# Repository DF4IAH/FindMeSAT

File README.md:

# FindMeSAT
GPS assisted tracking device with GSM (SMS & GPRS) and Bluetooth connectivity.

## List of devices
* __CPU: Atmel ATxmega256A3BU__ (256kB Flash / 16kB RAM / 4kB EEPROM)
* __GSM / GPS / BT: SIM808__ (SMS / GPRS / ...)
* __VHF/UHF: AX5243__ (VHF TX/RX)
* __Accel/Gyro/Mag: MPU-9250__ (3Axis-Acceleration, 3Axis-Gyro, 3Axis-Magneto)
* __Baro/Temp: MS560702BA03-50__ (0.2 meter height resolution, better than 0.01°C resolution)
* __Hygro: SHT31-DIS__ (hygrometer within the air stream of the board)
* __VCTCXO: CFPT-141_20MHz__ (being synchronized to the GPS 1PPS signal by pulling the VC)
* __GSM antenna: within the PCB__ (works for each band)
* __BT antenna: within the PCB__ (not used yet)
* __GPS antenna: external active antenna__ via MCX connector
* __VHF/UHF antenna: external passive antenna__ via SMA connector
* __LiPo: 1-cell 3.7V__ (high power request by the SIM808 device to be satisfied)

### Current PCB overview:

### Working Tracker application with GPRS, APRS and POCSAG transmission:

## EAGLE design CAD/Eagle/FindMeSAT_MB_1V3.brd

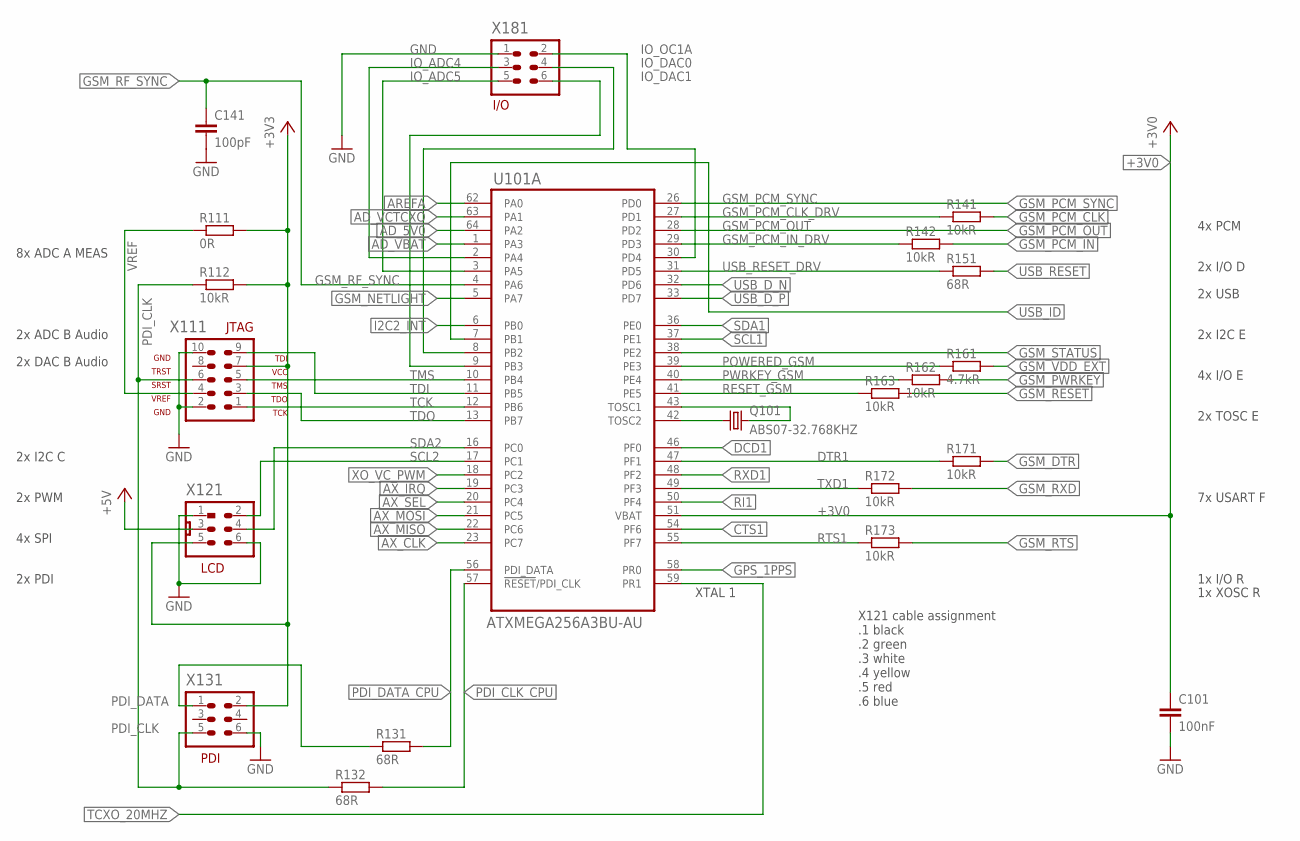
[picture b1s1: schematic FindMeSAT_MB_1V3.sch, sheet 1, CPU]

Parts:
C101: 100nF; C0603
C141: 100pF; C0603
Q101: ABS07-32.768KHZ; ABS07
R111: 0R; R0805
R112, R141, R142, R162, R163, R171, R172, R173: 10kR; R0603
R131, R132, R151: 68R; R0603
R161: 4.7kR; R0603
U101: ATXMEGA256A3BU-AU; QFP80P1600X1600X120-64N
X111: AVR-JTAG-10
X121: MOLEX_90130_2X03
X131, X181: HEADER-2X3; 2X03

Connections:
+3V0: C101.1, U101.51 (VBAT); also elsewhere on the board
+3V3: R111.2, R112.2, X111.7, X121.5, X131.2; also elsewhere on the board
+5V: X121.3; also elsewhere on the board
AD_5V0: U101.64 (PA2); also elsewhere on the board
AD_VBAT: U101.1 (PA3); also elsewhere on the board
AD_VCTCXO: U101.63 (PA1); also elsewhere on the board
AREFA: U101.62 (PA0); also elsewhere on the board
AX_CLK: U101.23 (PC7); also elsewhere on the board
AX_IRQ: U101.19 (PC3); also elsewhere on the board
AX_MISO: U101.22 (PC6); also elsewhere on the board
AX_MOSI: U101.21 (PC5); also elsewhere on the board
AX_SEL: U101.20 (PC4); also elsewhere on the board
CTS1: U101.54 (PF6); also elsewhere on the board
DCD1: U101.46 (PF0); also elsewhere on the board
DTR1: R171.1, U101.47 (PF1)
GND: C101.2, C141.2, X111.2, X111.10, X121.1, X121.6, X131.6, X181.1; also elsewhere on the board
GPS_1PPS: U101.58 (PR0); also elsewhere on the board
GSM_DTR: R171.2; also elsewhere on the board
GSM_NETLIGHT: U101.5 (PA7); also elsewhere on the board
GSM_PCM_CLK: R141.2; also elsewhere on the board
GSM_PCM_CLK_DRV: R141.1, U101.27 (PD1)
GSM_PCM_IN: R142.2; also elsewhere on the board
GSM_PCM_IN_DRV: R142.1, U101.29 (PD3)
GSM_PCM_OUT: U101.28 (PD2); also elsewhere on the board
GSM_PCM_SYNC: U101.26 (PD0); also elsewhere on the board
GSM_PWRKEY: R162.2; also elsewhere on the board
GSM_RESET: R163.2; also elsewhere on the board
GSM_RF_SYNC: C141.1, U101.4 (PA6); also elsewhere on the board
GSM_RTS: R173.2; also elsewhere on the board
GSM_RXD: R172.2; also elsewhere on the board
GSM_STATUS: U101.38 (PE2); also elsewhere on the board
GSM_VDD_EXT: R161.2; also elsewhere on the board
I2C2_INT: U101.6 (PB0); also elsewhere on the board
IO_ADC4: U101.2 (PA4), X181.3
IO_ADC5: U101.3 (PA5), X181.5
IO_DAC0: U101.8 (PB2), X181.4
IO_DAC1: U101.9 (PB3), X181.6
IO_OC1A: U101.30 (PD4), X181.2
PDI_CLK: R112.1, R132.1, X111.6, X131.5
PDI_CLK_CPU: R132.2, U101.57 (!RESET!/PDI_CLK)
PDI_DATA: R131.1, X131.1
PDI_DATA_CPU: R131.2, U101.56 (PDI_DATA)
POWERED_GSM: R161.1, U101.39 (PE3)
PWRKEY_GSM: R162.1, U101.40 (PE4)
RESET_GSM: R163.1, U101.41 (PE5)
RI1: U101.50 (PF4); also elsewhere on the board
RTS1: R173.1, U101.55 (PF7)
RXD1: U101.48 (PF2); also elsewhere on the board
SCL1: U101.37 (PE1); also elsewhere on the board
SCL2: U101.17 (PC1), X121.2
SDA1: U101.36 (PE0); also elsewhere on the board
SDA2: U101.16 (PC0), X121.4
TCK: U101.12 (PB6), X111.1
TCXO_20MHZ: U101.59 (PR1); also elsewhere on the board
TDI: U101.11 (PB5), X111.9
TDO: U101.13 (PB7), X111.3
TMS: U101.10 (PB4), X111.5
TOSC1: Q101.2, U101.43 (TOSC1)
TOSC2: Q101.1, U101.42 (TOSC2)
TXD1: R172.1, U101.49 (PF3)
USB_D_N: U101.32 (PD6); also elsewhere on the board
USB_D_P: U101.33 (PD7); also elsewhere on the board
USB_ID: U101.7 (PB1); also elsewhere on the board
USB_RESET: R151.2; also elsewhere on the board
USB_RESET_DRV: R151.1, U101.31 (PD5)
VREF: R111.1, X111.4
XO_VC_PWM: U101.18 (PC2); also elsewhere on the board

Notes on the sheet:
XTAL 1
PDI
2x ADC B Audio
8x ADC A MEAS
2x PWM
4x SPI
2x I2C C
2x I2C E
2x USB
4x PCM
7x USART F
4x I/O E
2x TOSC E
1x I/O R
1x XOSC R
2x I/O D
2x PDI
2x DAC B Audio
LCD
I/O
X121 cable assignment .1 black .2 green .3 white .4 yellow .5 red .6 blue

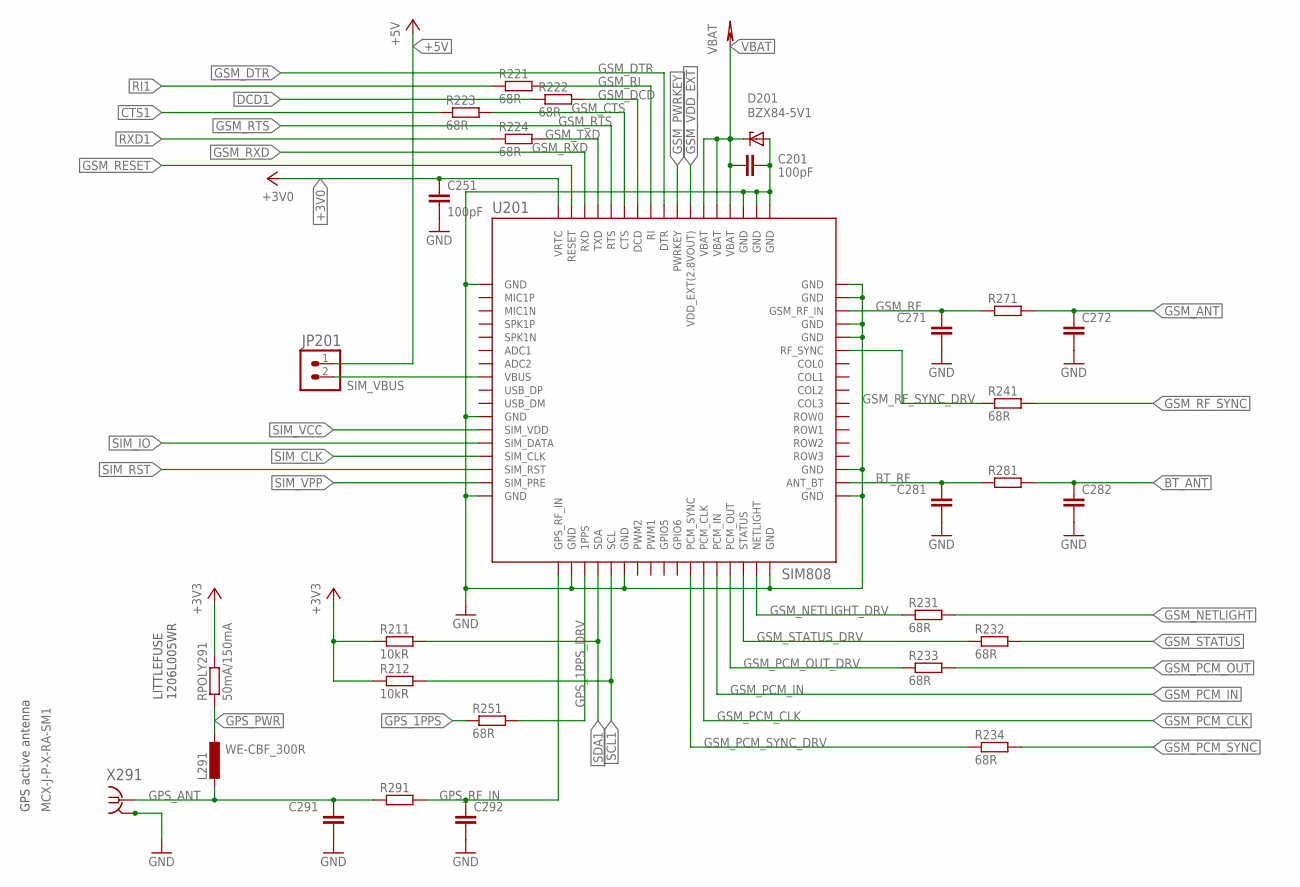
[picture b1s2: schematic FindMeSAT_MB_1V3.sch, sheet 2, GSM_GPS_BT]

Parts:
C201, C251: 100pF; C0603
C271, C272, C281, C282, C291, C292: C-EUC0603; C0603
D201: BZX84-5V1; TO236
JP201: POW; 1X02
L291: WE-CBF_300R; L3216C
R211, R212: 10kR; R0603
R221, R222, R223, R224, R231, R232, R233, R234, R241, R251: 68R; R0603
R271, R281: R-EU_R0805; R0805
R291: R-EU_R0603; R0603
RPOLY291: 50mA/150mA; R1210
U201: SIM808
X291: MCX-J-P-X-RA-SM1

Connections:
+3V0: C251.1, U201.17 (VRTC); also elsewhere on the board
+3V3: R211.1, R212.1, RPOLY291.2; also elsewhere on the board
+5V: JP201.1; also elsewhere on the board
BT_ANT: C282.1, R281.2
BT_RF: C281.1, R281.1, U201.53 (ANT_BT)
CTS1: R223.1; also elsewhere on the board
DCD1: R222.1; also elsewhere on the board
GND: C201.2, C251.2, C271.2, C272.2, C281.2, C282.2, C291.2, C292.2, D201.A, U201.1 (GND), U201.2 (GND), U201.3 (GND), U201.18 (GND), U201.28 (GND), U201.34 (GND), U201.36 (GND), U201.40 (GND), U201.51 (GND), U201.52 (GND), U201.54 (GND), U201.64 (GND), U201.65 (GND), U201.67 (GND), U201.68 (GND), X291.2, X291.3, X291.4, X291.5; also elsewhere on the board
GPS_1PPS: R251.1; also elsewhere on the board
GPS_1PPS_DRV: R251.2, U201.37 (1PPS)
GPS_ANT: C291.1, L291.2, R291.1, X291.1
GPS_PWR: L291.1, RPOLY291.1
GPS_RF_IN: C292.1, R291.2, U201.35 (GPS_RF_IN)
GSM_ANT: C272.1, R271.2
GSM_CTS: R223.2, U201.12 (CTS)
GSM_DCD: R222.2, U201.11 (DCD)
GSM_DTR: U201.9 (DTR); also elsewhere on the board
GSM_NETLIGHT: R231.2; also elsewhere on the board
GSM_NETLIGHT_DRV: R231.1, U201.50 (NETLIGHT)
GSM_PCM_CLK: U201.46 (PCM_CLK); also elsewhere on the board
GSM_PCM_IN: U201.47 (PCM_IN); also elsewhere on the board
GSM_PCM_OUT: R233.2; also elsewhere on the board
GSM_PCM_OUT_DRV: R233.1, U201.48 (PCM_OUT)
GSM_PCM_SYNC: R234.2; also elsewhere on the board
GSM_PCM_SYNC_DRV: R234.1, U201.45 (PCM_SYNC)
GSM_PWRKEY: U201.8 (PWRKEY); also elsewhere on the board
GSM_RESET: U201.16 (RESET); also elsewhere on the board
GSM_RF: C271.1, R271.1, U201.66 (GSM_RF_IN)
GSM_RF_SYNC: R241.2; also elsewhere on the board
GSM_RF_SYNC_DRV: R241.1, U201.63 (RF_SYNC)
GSM_RI: R221.2, U201.10 (RI)
GSM_RTS: U201.13 (RTS); also elsewhere on the board
GSM_RXD: U201.15 (RXD); also elsewhere on the board
GSM_STATUS: R232.2; also elsewhere on the board
GSM_STATUS_DRV: R232.1, U201.49 (STATUS)
GSM_TXD: R224.2, U201.14 (TXD)
GSM_VDD_EXT: U201.7 (VDD_EXT(2.8VOUT)); also elsewhere on the board
RI1: R221.1; also elsewhere on the board
RXD1: R224.1; also elsewhere on the board
SCL1: R212.2, U201.39 (SCL); also elsewhere on the board
SDA1: R211.2, U201.38 (SDA); also elsewhere on the board
SIM_CLK: U201.31 (SIM_CLK); also elsewhere on the board
SIM_IO: U201.30 (SIM_DATA); also elsewhere on the board
SIM_RST: U201.32 (SIM_RST); also elsewhere on the board
SIM_VBUS: JP201.2, U201.25 (VBUS)
SIM_VCC: U201.29 (SIM_VDD); also elsewhere on the board
SIM_VPP: U201.33 (SIM_PRE); also elsewhere on the board
VBAT: C201.1, D201.C, U201.4 (VBAT), U201.5 (VBAT), U201.6 (VBAT); also elsewhere on the board

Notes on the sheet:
LITTLEFUSE 1206L005WR
GPS active antenna

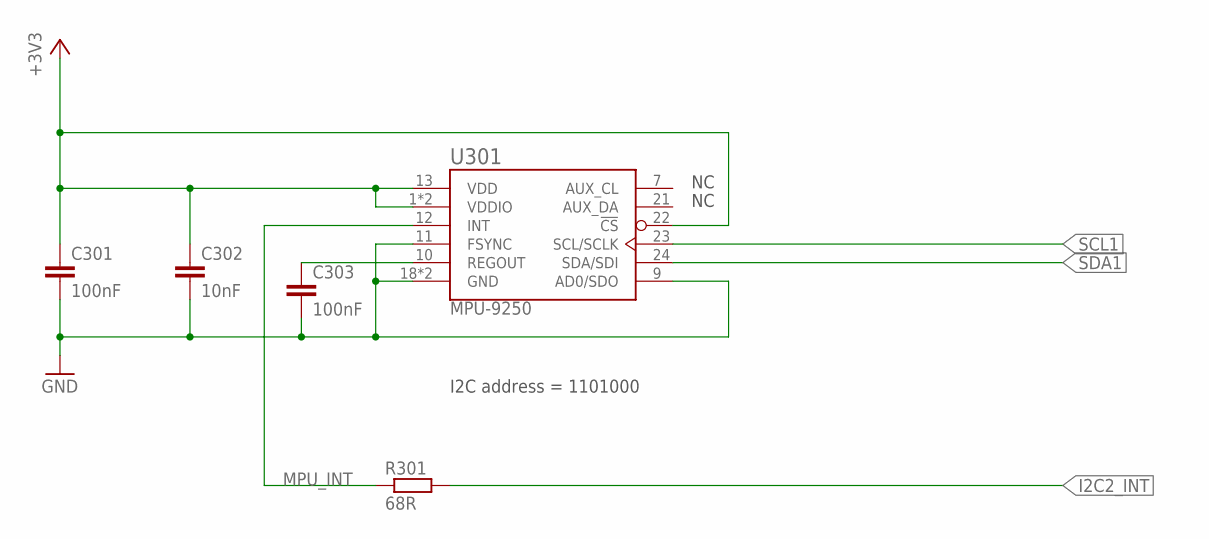
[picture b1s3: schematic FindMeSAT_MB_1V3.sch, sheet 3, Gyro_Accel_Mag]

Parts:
C301, C303: 100nF; C0603
C302: 10nF; C0603
R301: 68R; R0603
U301: MPU-9250; QFN24-3X3

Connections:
+3V3: C301.1, C302.1, U301.1 (VDDIO), U301.8 (VDDIO), U301.13 (VDD), U301.22 (!CS); also elsewhere on the board
GAM_RO: C303.1, U301.10 (REGOUT)
GND: C301.2, C302.2, C303.2, U301.9 (AD0/SDO), U301.11 (FSYNC), U301.18 (GND), U301.20 (GND); also elsewhere on the board
I2C2_INT: R301.2; also elsewhere on the board
MPU_INT: R301.1, U301.12 (INT)
SCL1: U301.23 (SCL/SCLK); also elsewhere on the board
SDA1: U301.24 (SDA/SDI); also elsewhere on the board

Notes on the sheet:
I2C address = 1101000

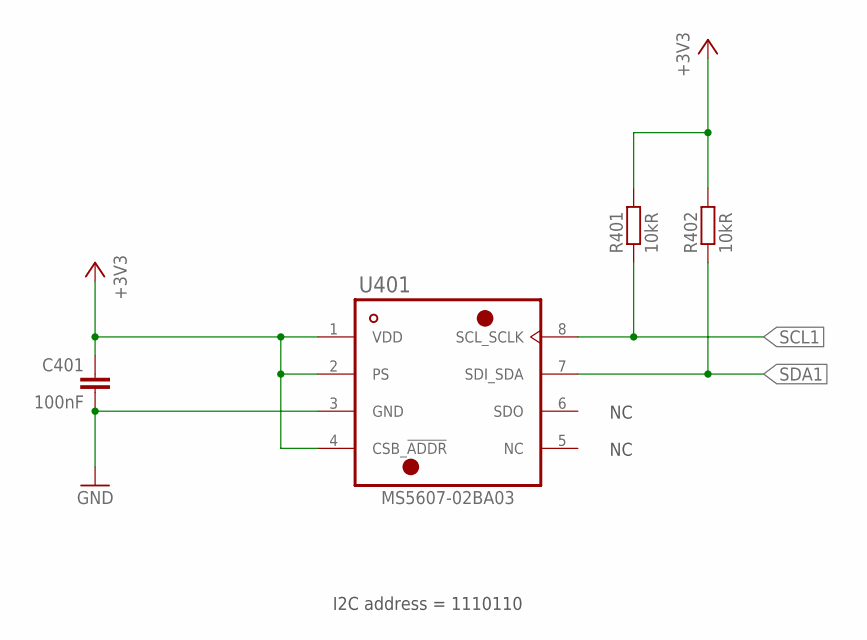
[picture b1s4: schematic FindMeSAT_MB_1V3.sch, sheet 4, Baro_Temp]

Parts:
C401: 100nF; C0603
R401, R402: 10kR; R0603
U401: MS5607-02BA03; MS5607-02BA

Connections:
+3V3: C401.1, R401.2, R402.2, U401.1 (VDD), U401.2 (PS), U401.4 (CSB_!ADDR); also elsewhere on the board
GND: C401.2, U401.3 (GND); also elsewhere on the board
SCL1: R401.1, U401.8 (SCL_SCLK); also elsewhere on the board
SDA1: R402.1, U401.7 (SDI_SDA); also elsewhere on the board

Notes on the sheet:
I2C address = 1110110

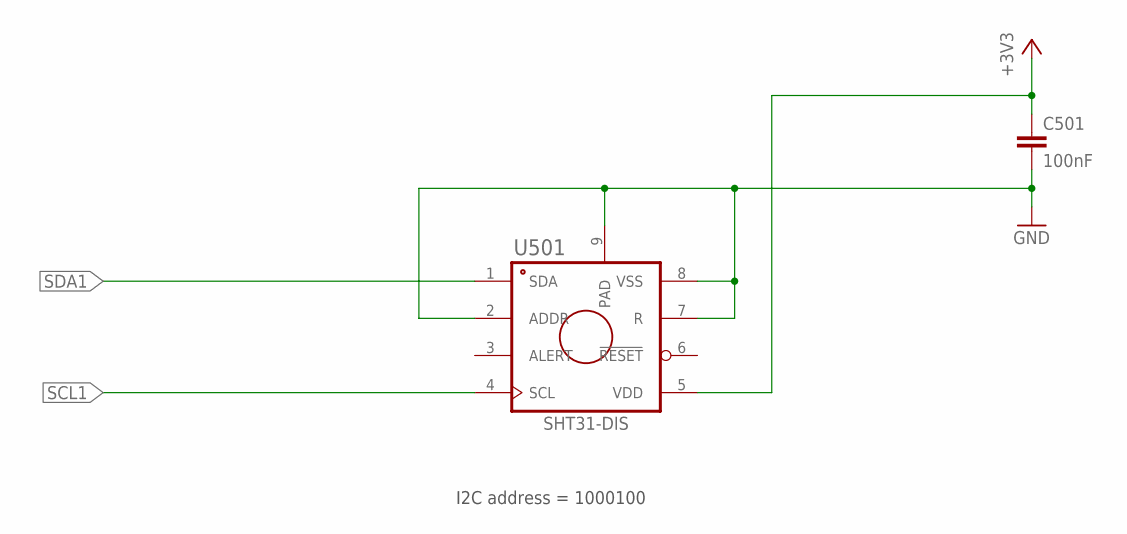
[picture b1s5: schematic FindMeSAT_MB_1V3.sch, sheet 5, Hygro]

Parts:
C501: 100nF; C0603
U501: SHT31-DIS; DFN8/SHT

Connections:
+3V3: C501.1, U501.5 (VDD); also elsewhere on the board
GND: C501.2, U501.2 (ADDR), U501.7 (R), U501.8 (VSS), U501.9 (PAD); also elsewhere on the board
SCL1: U501.4 (SCL); also elsewhere on the board
SDA1: U501.1 (SDA); also elsewhere on the board

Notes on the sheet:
I2C address = 1000100

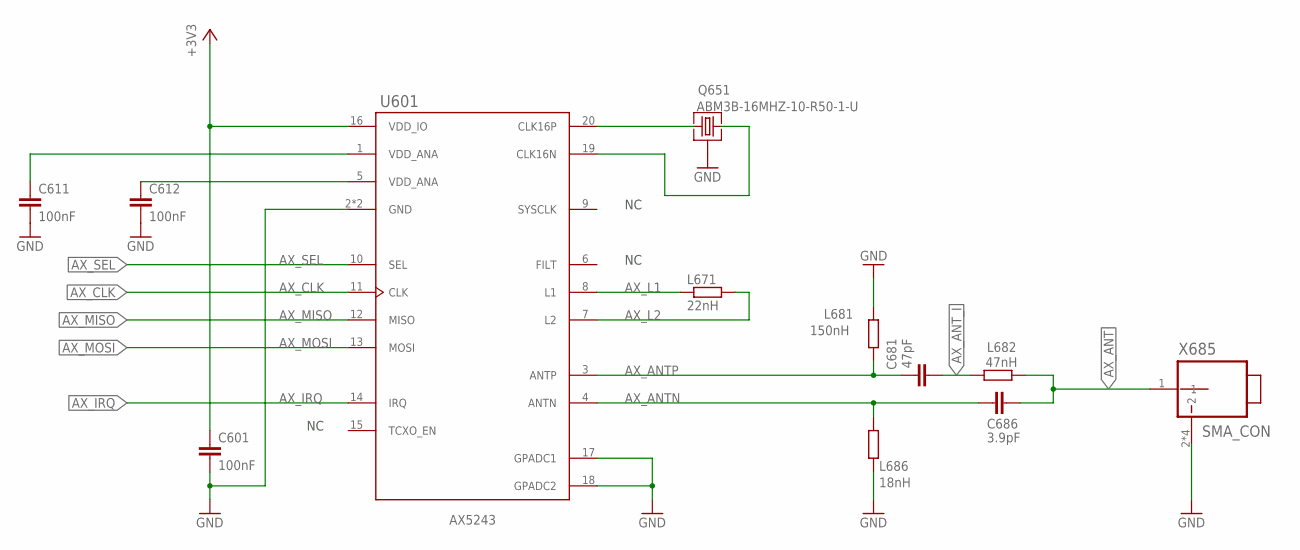
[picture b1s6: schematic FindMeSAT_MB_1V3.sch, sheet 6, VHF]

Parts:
C601, C611, C612: 100nF; C0603
C681: 47pF; C0603
C686: 3.9pF; C0603
L671: 22nH; R0603
L681: 150nH; R0603
L682: 47nH; R0603
L686: 18nH; R0603
Q651: ABM3B-16MHZ-10-R50-1-U; ABM03B
U601: AX5243; QFN20-4X4-0P5-PAD
X685: SMA_CON; SMA_SMT_AMPHENOL_901-143

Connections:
+3V3: C601.1, U601.16 (VDD_IO); also elsewhere on the board
AX_ANT: C686.2, L682.2, X685.1
AX_ANTN: C686.1, L686.2, U601.4 (ANTN)
AX_ANTP: C681.1, L681.1, U601.3 (ANTP)
AX_ANT_I: C681.2, L682.1
AX_CLK: U601.11 (CLK); also elsewhere on the board
AX_IRQ: U601.14 (IRQ); also elsewhere on the board
AX_L1: L671.1, U601.8 (L1)
AX_L2: L671.2, U601.7 (L2)
AX_MISO: U601.12 (MISO); also elsewhere on the board
AX_MOSI: U601.13 (MOSI); also elsewhere on the board
AX_SEL: U601.10 (SEL); also elsewhere on the board
CLK16N: Q651.3 (2), U601.19 (CLK16N)
CLK16P: Q651.1, U601.20 (CLK16P)
GND: C601.2, C611.2, C612.2, L681.2, L686.1, Q651.2 (3), Q651.4 (3), U601.2 (GND), U601.17 (GPADC1), U601.18 (GPADC2), U601.21 (GND), X685.2, X685.3 (2), X685.4 (2), X685.5 (2); also elsewhere on the board
VDD_ANA@1: C611.1, U601.1 (VDD_ANA)
VDD_ANA@5: C612.1, U601.5 (VDD_ANA)

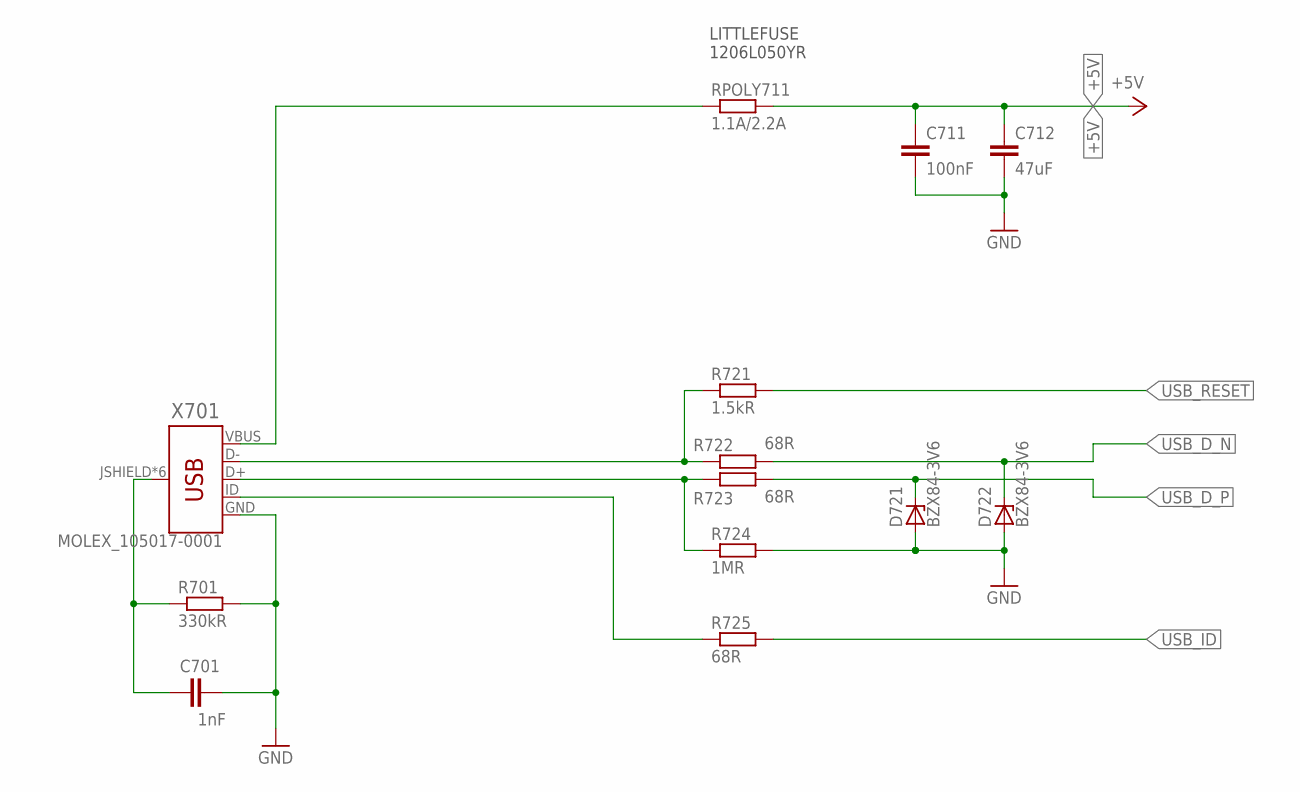
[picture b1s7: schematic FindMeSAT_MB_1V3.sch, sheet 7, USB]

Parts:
C701: 1nF; C0603
C711: 100nF; C0603
C712: 47uF; C0805
D721, D722: BZX84-3V6; TO236
R701: 330kR; R0603
R721: 1.5kR; R0603
R722, R723, R725: 68R; R0603
R724: 1MR; R0603
RPOLY711: 1.1A/2.2A; M1206
X701: MOLEX_105017-0001; USB-B-MICRO-SMD_MOLEX-105017-0001

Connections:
+5V: C711.1, C712.1, RPOLY711.2; also elsewhere on the board
GND: C701.2, C711.2, C712.2, D721.A, D722.A, R701.2, R724.2, X701.GND; also elsewhere on the board
J_D+: R723.1, R724.1, X701.D+ (J_D+)
J_D-: R721.1, R722.1, X701.D- (J_D-)
J_ID: R725.1, X701.ID (J_ID)
J_SHIELD: C701.1, R701.1, X701.JSHIELD (SHIELD), X701.JSHIELD@2 (SHIELD), X701.JSHIELD@3 (SHIELD), X701.JSHIELD@4 (SHIELD), X701.JSHIELD@5 (SHIELD), X701.JSHIELD@6 (SHIELD)
J_VUSB: RPOLY711.1, X701.VBUS (J_VUSB)
USB_D_N: D722.C, R722.2; also elsewhere on the board
USB_D_P: D721.C, R723.2; also elsewhere on the board
USB_ID: R725.2; also elsewhere on the board
USB_RESET: R721.2; also elsewhere on the board

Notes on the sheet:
LITTLEFUSE 1206L050YR

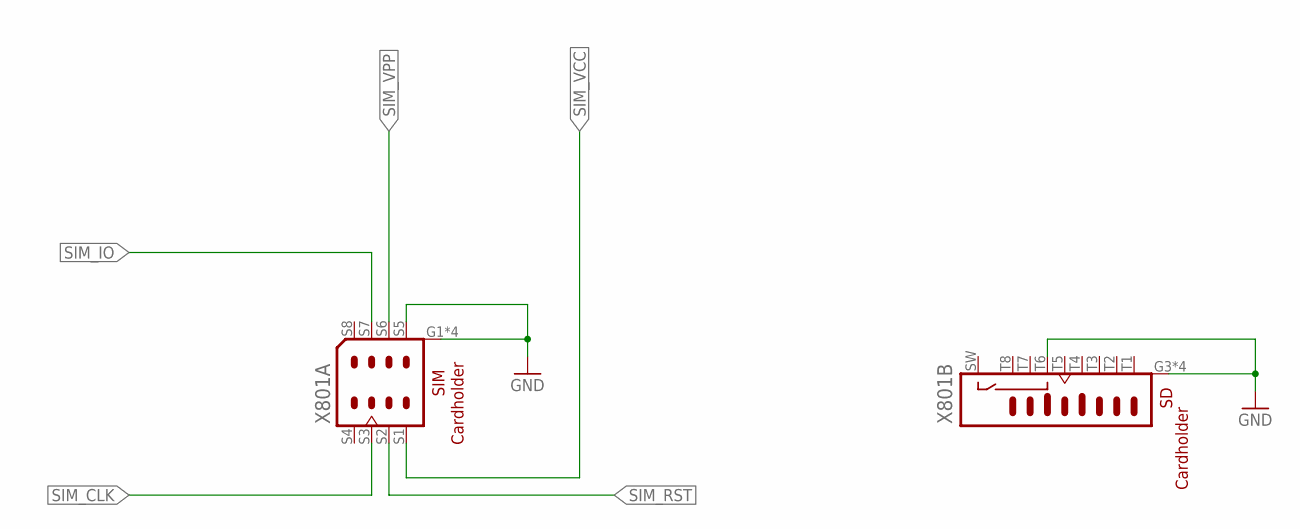
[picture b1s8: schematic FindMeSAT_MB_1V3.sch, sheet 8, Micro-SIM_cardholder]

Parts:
X801: MICROSIM-8P_SDCARD-8P_MOLEX-104642-1610

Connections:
GND: X801.G1 (SHIELD), X801.G2 (SHIELD), X801.G3 (SHIELD), X801.G4 (SHIELD), X801.G5 (SHIELD), X801.G6 (SHIELD), X801.G7 (SHIELD), X801.G8 (SHIELD), X801.S5, X801.T6; also elsewhere on the board
SIM_CLK: X801.S3; also elsewhere on the board
SIM_IO: X801.S7; also elsewhere on the board
SIM_RST: X801.S2; also elsewhere on the board
SIM_VCC: X801.S1; also elsewhere on the board
SIM_VPP: X801.S6; also elsewhere on the board
T4: X801.T4

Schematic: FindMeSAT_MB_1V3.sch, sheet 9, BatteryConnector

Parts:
C901: 100uF; C0805
RPOLY901: 1.1A/2.2A; M1206
X901: JST_S3B-XH-A

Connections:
BATTERY: RPOLY901.1, X901.1
GND: C901.2, X901.3; also elsewhere on the board
VBAT: C901.1, RPOLY901.2; also elsewhere on the board

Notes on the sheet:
LITTLEFUSE 1206L110THYR

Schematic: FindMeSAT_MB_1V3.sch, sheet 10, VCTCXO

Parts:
C1001: 10uF; C0805
C1002, C1012: 100nF; C0603
C1011: 100pF; C0603
R1001, R1011: 100kR; R0603
R1002: 10kR; R0603
R1012: 330kR; R0603
R1013: 47R; R0603
R1021: 27R; R0603
U1001: CFPT-141-20MHZ; CFPT-141
U1011, U1021: OPA354; SOT-23-5

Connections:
+3V0: C1002.1, U1001.4 (VCC_3V0); also elsewhere on the board
+3V3: C1012.1, R1012.2, U1011.5 (V+), U1021.5 (V+); also elsewhere on the board
AD_VCTCXO: R1021.2, U1021.1 (OUT); also elsewhere on the board
GND: C1001.2, C1002.2, C1011.2, C1012.2, R1011.1, U1001.2 (GND), U1011.2 (V-), U1021.2 (V-); also elsewhere on the board
TCXO_20MHZ: R1013.2; also elsewhere on the board
TRSH: C1011.1, R1011.2, R1012.1, U1011.4 (-IN)
VC_OP_FB: R1021.1, U1021.4 (-IN)
XO_AMP: R1013.1, U1011.1 (OUT)
XO_DRV: U1001.3 (OUT), U1011.3 (+IN)
XO_LP: C1001.1, R1001.2, R1002.1, U1021.3 (+IN)
XO_VC: R1002.2, U1001.1 (VC)
XO_VC_PWM: R1001.1; also elsewhere on the board

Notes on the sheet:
f_LP = 1 Hz, PWM min. 100 Hz
905mV

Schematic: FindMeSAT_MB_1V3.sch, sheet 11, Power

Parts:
C191, C192, C193, C194, C195, C196, C1112, C1121: 100nF; C0603
C1111, C1113: 47uF; C0805
C1141: 100pF; C0603
D1111, D1121, D1122: CRS08; SOD80C
L191: 10uH; R0603
L1111: 4.7uH; L5650M
R1111, R1131: 4.02kR; R0603
R1112, R1132: 6.04kR; R0603
R1113: 100kR; R0603
R1114: 15kR; R0603
R1115: 68kR; R0603
R1142: 2.0kR; R0603
U101: ATXMEGA256A3BU-AU; QFP80P1600X1600X120-64N
U1111: LM2831YMF; SOT95P280X145-5N
U1121: LM4120IM5-3.0; SOT95P285X120-5N

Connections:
+3V0: R1142.2, U1121.5 (VOUT); also elsewhere on the board
+3V3: C191.1, C192.1, C193.1, C194.1, C195.1, C1112.1, C1113.1, L191.2, L1111.1, R1115.2, U101.15 (VCC_1), U101.25 (VCC_2), U101.35 (VCC_3), U101.45 (VCC_4), U101.53 (VCC_5); also elsewhere on the board
+5V: D1121.A, R1112.2; also elsewhere on the board
AD_5V0: R1111.2, R1112.1; also elsewhere on the board
AD_VBAT: R1131.1, R1132.2; also elsewhere on the board
AREFA: C1141.1, R1142.1; also elsewhere on the board
AVCC: C196.1, L191.1, U101.61 (AVCC)
EN: R1113.2, U1111.4 (EN)
FB: R1114.2, R1115.1, U1111.3 (FB)
GND: C191.2, C192.2, C193.2, C194.2, C195.2, C196.2, C1111.2, C1112.2, C1113.2, C1121.2, C1141.2, D1111.A, R1111.1, R1114.1, R1131.2, U101.14 (GND_1), U101.24 (GND_2), U101.34 (GND_3), U101.44 (GND_4), U101.52 (GND_5), U101.60 (GND_6), U1111.2 (GND), U1121.2 (GND); also elsewhere on the board
SW: D1111.C, L1111.2, U1111.1 (SW)
VBAT: D1122.A, R1132.1; also elsewhere on the board
VIN: C1111.1, C1121.1, D1121.C, D1122.C, R1113.1, U1111.5 (VIN), U1121.3 (EN), U1121.4 (VIN)

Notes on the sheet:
0.6V
1:0.4 = 2.0V
AREF for ADCA

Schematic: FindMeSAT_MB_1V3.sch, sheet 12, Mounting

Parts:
FM1201, FM1202, FM1203, FM1204: FIDUCIAL_MARK_1MM
H1201, H1203, H1204: MOUNT-PAD-ROUND2.8; 2,8-PAD

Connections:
GND: H1201.B2,8, H1203.B2,8, H1204.B2,8; also elsewhere on the board

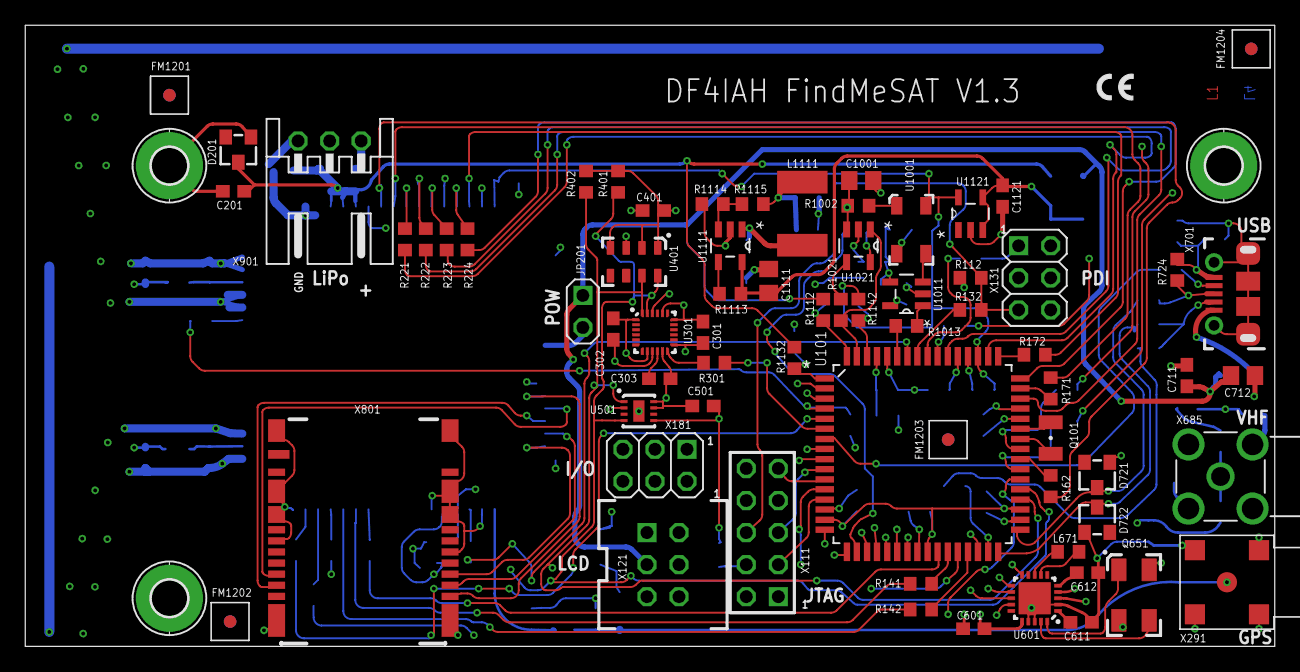
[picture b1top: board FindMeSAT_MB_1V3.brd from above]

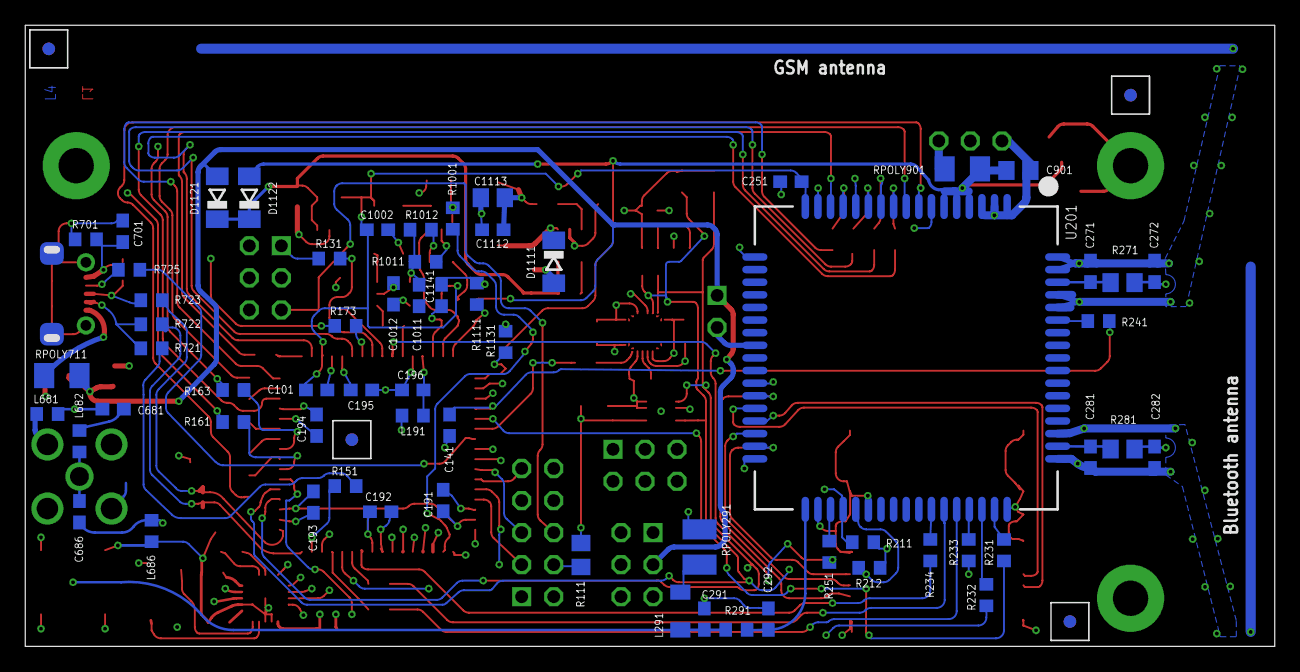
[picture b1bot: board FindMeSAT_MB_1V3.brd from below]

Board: 4 copper layers, 98.4 x 48.6 mm, 136 parts (64 on the bottom side), 120 nets.

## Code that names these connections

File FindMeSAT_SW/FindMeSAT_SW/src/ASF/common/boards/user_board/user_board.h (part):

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 * an RC low-pass circuit feeded by a PWM signal.
 */
//@{
#define XO_VC_PWM_GPIO                  IOPORT_CREATE_PIN(PORTC, 2)
#define XO_VC_PWM                       XO_VC_PWM_GPIO
//@}

/**
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 * The SIM808 is a GMS/BT/GPS device.
 */
//@{
#define GSM_RF_SYNC_GPIO				IOPORT_CREATE_PIN(PORTA, 6)
#define GSM_NETLIGHT_GPIO				IOPORT_CREATE_PIN(PORTA, 7)
#define GSM_PCM_SYNC_GPIO				IOPORT_CREATE_PIN(PORTD, 0)
#define GSM_PCM_CLK_DRV_GPIO			IOPORT_CREATE_PIN(PORTD, 1)
#define GSM_PCM_OUT_GPIO				IOPORT_CREATE_PIN(PORTD, 2)
#define GSM_PCM_IN_DRV_GPIO				IOPORT_CREATE_PIN(PORTD, 3)
#define GSM_POWERED_GPIO				IOPORT_CREATE_PIN(PORTE, 3)
#define GSM_PWRKEY_DRV_GPIO				IOPORT_CREATE_PIN(PORTE, 4)
#define GSM_RESET_DRV_GPIO				IOPORT_CREATE_PIN(PORTE, 5)
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#define GSM_RTS1_DRV_GPIO				IOPORT_CREATE_PIN(PORTF, 7)
#define GPS_GSM_1PPS_GPIO				IOPORT_CREATE_PIN(PORTR, 0)

#define GSM_RF_SYNC						GSM_RF_SYNC_GPIO
#define GSM_NETLIGHT					GSM_NETLIGHT_GPIO
#define GSM_PCM_SYNC					GSM_PCM_SYNC_GPIO
#define GSM_PCM_CLK_DRV					GSM_PCM_CLK_DRV_GPIO
#define GSM_PCM_OUT						GSM_PCM_OUT_GPIO
#define GSM_PCM_IN_DRV					GSM_PCM_IN_DRV_GPIO
#define GSM_POWERED						GSM_POWERED_GPIO
#define GSM_PWRKEY_DRV					GSM_PWRKEY_DRV_GPIO
#define GSM_RESET_DRV					GSM_RESET_DRV_GPIO
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 * USB lines for controlling and communication with the USB port.
 */
//@{
#define USB_ID_GPIO                     IOPORT_CREATE_PIN(PORTB, 1)
#define USB_RESET_DRV_GPIO              IOPORT_CREATE_PIN(PORTD, 5)
#define USB_D_N_GPIO                    IOPORT_CREATE_PIN(PORTD, 6)
#define USB_D_P_GPIO                    IOPORT_CREATE_PIN(PORTD, 7)

#if 0
#define USB_ID                          USB_ID_GPIO
#define USB_RESET_DRV                   USB_RESET_DRV_GPIO
#define USB_D_N                         USB_D_N_GPIO
#define USB_D_P                         USB_D_P_GPIO
#endif
//@}

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#define I2C2_USART_SCL                  &USARTC0
#define SDA2_GPIO                       IOPORT_CREATE_PIN(PORTC, 0)
#define SCL2_GPIO                       IOPORT_CREATE_PIN(PORTC, 1)
#define I2C2_INT_GPIO                   IOPORT_CREATE_PIN(PORTB, 0)

#define I2C2_INT                        I2C2_INT_GPIO
//@}


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//@{
#define AX_SPI                          &SPIC
#define AX_SPI_CLK                      &USARTC1
#define AX_IRQ_PIN                      IOPORT_CREATE_PIN(PORTC, 3)
#define AX_SEL_PIN                      IOPORT_CREATE_PIN(PORTC, 4)
#define AX_MOSI_PIN                     IOPORT_CREATE_PIN(PORTC, 5)
#define AX_MISO_PIN                     IOPORT_CREATE_PIN(PORTC, 6)
#define AX_CLK_PIN                      IOPORT_CREATE_PIN(PORTC, 7)

#define AX_IRQ                          AX_IRQ_PIN
#define AX_SEL                          AX_SEL_PIN
#define AX_MOSI                         AX_MOSI_PIN
#define AX_MISO                         AX_MISO_PIN
#define AX_CLK                          AX_CLK_PIN

#if 0
#define AX_INTC_INIT()                  ioport_configure_pin(AX_IRQ_PIN, IOPORT_DIR_INPUT); \
										PORTC.PIN3CTRL = PORT_ISC0_bm; \
										PORTC.INT0MASK = PIN3_bm; \
										PORTC.INTFLAGS = PORT_INT0IF_bm;
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
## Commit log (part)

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2017-10-07 SW - position, height and speed added
2017-10-07 SW - remove empty lines after GNSINF messages
2017-10-09 SW - APRS messaging continued
2017-10-14 SW - APRS - callsign added to message
2017-11-02 SW - QNH and Dew Point temperature added, APRS messages enhanced
2017-11-03 SW - 9-axis mag - correction factor for Z equalized to X and Y values with much better results (2)
2017-11-05 SW - environmental temperature delta being set by command line
2017-11-05 SW - environment temperature bug fixed
2017-11-07 SW - APRS - now data is sent to one of the APRS servers and presented at http://aprs.fi/
2017-11-07 SW - APRS - boot up optimized
2017-11-07 SW - comes up with or without LCD
2017-11-10 SW - APRS - timings enhanced (2)
2017-11-10 SW - APRS - N4 with WX data with its own SSID -11 (balloon)
2017-11-12 SW - serial - switched from ASF to own implementation with interrupt handling
2017-11-16 SW - serial - some code fixed to be re-entrant robust - coming up OK - APRS message still corrupted
2017-11-19 HW_V1.3 - cable assignment for LCD-cable X-121 added
2017-11-25 SW - LCD - shutdown and reset info with power down of the LCD
2017-11-26 SW - TWI/9xis - power-up callibration very good, TODO: TWI some time later halts --> remove TWI library and write own async-code
2017-11-26 SW - TWI - new code for MASTER transmit() written, untested
2017-12-05 Revert "SW - TWI - build environment has changed due to TWI change"
    This reverts commit be31e14b14db9af95ee572b3cabf2aba95613b3a.
2017-12-05 Revert "SW - TWI - new code for MASTER transmit() written, untested"
    This reverts commit b16aff358120904b78d6b26a77b39b159b45dc13.
2017-12-05 SW - revert - best of the reverted applied
2017-12-05 SW - APRS/RING - when ringing to FindMeSAT do first APRS packet twice, when aprs=ring then once only
2017-12-05 SW - TWI1 9axis - accelXYZ calibration enhanced
2017-12-18 SW - first characters are coming in (2)
2017-12-19 SW - SIM808 SER - new data rate is 57.600 bits/sec
2017-12-19 Revert "SW - SIM808 Ser RX DMA - unreliable data transfer - to be reverted to IRQ variant"
    This reverts commit 28d0568286bbb5d2b08c0a0a167effc4865ec433.
2017-12-19 Revert "SW - SIM808 SER - new data rate is 57.600 bits/sec"
    This reverts commit 716218e8486f8edd17ed567bb40d26140da2aeaa.
2017-12-19 Revert "SW - first characters are coming in (2)"
    This reverts commit cec76d550794e149a866a9d67a98b826b36d7bd7.
2017-12-27 SW - SPI_AX - spi_ax.* added, initial setup done
2017-12-27 SW - SPI_AX - first successful read and write operations
2017-12-28 SW - SPI_AX - reduce SPI clock to 10 MHz (AX5243 spec, low power mode)
2017-12-31 SW - SPI_AX - some buggy SPI communication fixed
2018-01-01 SW - SPI_AX - first try to transmit works, too
2018-01-04 SW - SPI_AX - AX5243 transmitter comes up, FSK only, AFSK not working yet
2018-01-05 SW - SPI_AX - AX5243 - first packet radio UI packet with APRS information working?
2018-01-06 SW - SPI_AX - AX5243 - more on CRC to do
2018-01-06 SW - SPI_AX - AX5243 - different FRAMING modes tested, HDLC [1] nice to be used
2018-01-07 SW - SPI_AX - AX5243 - APRS TX - dummy APRS packet activated
2018-01-07 SW - SPI_AX - AX5243 - AXRadioLab configuration file added
2018-01-08 SW - SPI_AX - AX5243 - Test for the day: APRS/10 sec with more power
2018-01-11 SW - SPI_AX - AX5243 - POCSAG receive settings made
2018-01-15 SW - SPI_AX - AX5243 - POCSAG - sending messages to RIC
2018-01-15 SW - main application activated, AX5243 integration done
2018-01-17 SW - SIM808 - re-activated
2018-01-24 SW - AX5243 - POCSAG - Running with test message
2018-02-07 SW - DAPNET-POCSAG TimeSlot calculator (2)
2018-02-10 SW - DAPNET-POCSAG TimeSlot calculator - update of DB0CPU (old FunkRufMaster software)
2018-02-11 SW - DAPNET-POCSAG TimeSlot calculator - table line removed
2018-02-11 SW - POCSAG - modulation corrections done, source code
2018-02-12 SW - APRS & POCSAG & GPRS - coming up together as a GPS-Tracker
2018-02-13 SW - USB - blocking application when no USB is attached fixed
2018-02-14 SW - AX5243/POCSAG - messages can be sent, chiming every minute if desired, sending Skyper activation
2018-02-15 SW - AX5243/POCSAG - text presentation enhanced
2018-02-15 SW - AX5243/POCSAG - GPS Tracking to individual RIC and/or public rubric 95:Tracking
2018-02-16 SW - AX5243/POCSAG - news formatting changed, udi_cdc.c reverted due to reboots
2018-02-18 SW - SIM808/GPS - returned speed is km/h, not knots
2018-02-22 SW - TWI2/Gfx - before and after calibration doing Gfx updates
2018-02-23 DOCS - V1.2 - Screenshot of Eagle design added
2018-02-23 DOCS - @eaDir added to .gitignore
2018-02-24 SW - AX5243 RX - first RX code written
2018-03-06 DOCS - some missing weblinks included
2018-03-10 SW - ASF - making code more robust for cases where chip does not exist
2018-03-10 SW - ADC - make comment clear about the AREFA voltage
2018-03-11 SW - SPI/AX5243 - missing modes for TX added
2018-03-12 SW - SPI/AX5243 - full tracking operations working well again
2018-03-12 DOCS - Live application picture added
2018-03-12 DOCS - README.md updated
2018-03-16 SW - SPI/AX5243 - pocsag beacon function added
2018-03-18 SW - SPI/AX5243 - boot-up code modified
2018-03-22 SW - SPI/AX5243 - RX monitoring loop running
2018-03-25 SW - SPI/AX5243 - POCSAG: some enable flags fixed
2018-03-27 SW - SPI/AX5243 - POCSAG: some fixes made on decoder
2018-03-29 SW - SPI/AX5243 - POCSAG: outer chunks handling done
2018-03-30 SW - SPI/AX5243 - POCSAG: remove empty TX CODEWORDS
2018-03-30 SW - SPI/AX5243 - POCSAG: multiple minor fixes
2018-03-31 HW_V1.3 - one inductivity reversed to 150nH
2018-04-01 SW - SPI/AX5243 - POCSAG: decoding of alpha and numbers working
2018-04-07 HW_V1.2 - AX5243 UHF matching unit enhanced
2018-04-16 SW - SPI/AX5243 - POCSAG: decoding enhanced, skyper rubrics and news decoder added
2018-04-21 SW - V2 TrueSTUDIO - STM32CubeMX configuration based on the STM32L496-P Nucleo-144 board added
2018-04-21 SW - V2 TrueSTUDIO - clock domain settings done
2018-04-21 SW - SPI/AX5243 - POCSAG: skyper ALPHA/NEWS fixed(2)
2018-04-22 SW - V2 TrueSTUDIO - second export, problem with source directories
2018-04-25 SW - POCSAG - compilation
2018-04-25 SW - V2 TrueSTUDIO - board specific BSP directory added
2018-04-27 SW - output of TimeSlot enhanced
2018-04-28 SW - V2 TrueSTUDIO - FreeRTOS sessings changed
2018-04-29 SW - V2 TrueSTUDIO - USB CDC - Try to remove USB features not needed
2018-04-29 SW - V2 TrueSTUDIO - assert system activated
2018-04-30 SW - V2 TrueSTUDIO - Update to STM32CubeMX Version 4.25.0, more changes needed
2018-05-01 SW - output of TimeSlot enhanced (3)
2018-05-01 SW - V2 TrueSTUDIO - refactoring done
2018-05-01 SW - V2 TrueSTUDIO - 16MHz --> 80MHz
2018-05-01 SW - V2 TrueSTUDIO - RTOS - USB Queue sizes optimized
2018-05-01 SW - V2 TrueSTUDIO - interpreter module added
2018-05-02 SW - V2 TrueSTUDIO - startup code extended for Boot_RAM entry
2018-05-02 SW - V2 TrueSTUDIO - interpreter - cursor fixed, command names compare fixed
2018-05-03 SW - V2 TrueSTUDIO - ARM software reset added
2018-05-03 SW - V2 TrueSTUDIO - version information added
2018-05-04 SW - V2 TrueSTUDIO - display of device package added
2018-05-05 SW - V2 TrueSTUDIO - FLASH size info added
2018-05-05 SW - V2 TrueSTUDIO - MCU status for ADC values prepared
2018-05-06 SW - V2 TrueSTUDIO - spellings fixed
2018-05-08 SW - Config link removed
2018-05-10 SW - V2 TrueSTUDIO - no shield - I/O setup fixed
2018-05-11 SW - V2 TrueSTUDIO - SX1272 - first signal detected
2018-05-13 SW - V2 TrueSTUDIO - LoRaWAN - CRC added, RTC BKP registers assigned
2018-05-14 SW - V2 TrueSTUDIO - LoRaWAN - refactoring done
2018-05-14 SW - V2 TrueSTUDIO - LoRaWAN - more fixes
2018-05-15 SW - V2 TrueSTUDIO - LoRaWAN - chip settings multiple fixes
2018-05-17 SW - V2 TrueSTUDIO - LoRaWAN - 3x TX tries and RX listening on RX1/RX2
2018-05-20 SW - V2 TrueSTUDIO WIN - scripts and configurations modified
2018-05-21 SW - V2 TrueSTUDIO WIN - EXTI lines [15:10] activated and sent to IRQ (2)
2018-05-22 Merged from SW_21_SX1272_mbed_shield__LINUX
2018-05-26 SW - WirelessSensor_Decoder_kwmobile - RECORDING.sh script added also
2018-06-07 SW_21_SX1272_mbed_shield__WIN - randomized channel switching added
2018-06-08 SW_21_SX1272_mbed_shield__WIN - clean up of code done
2018-06-09 SW_21_SX1272_mbed_shield__WIN - SPI buffer handling refactored
2018-06-10 SW_21_SX1272_mbed_shield__WIN - radio programming refactored, decryption modes added
2018-06-15 SW_22_SX1276_mbed_shield__WIN - adaptions for SX1276 mbed shield done
2018-06-15 SW_22_SX1276_mbed_shield__WIN - some registers have changed assignments
2018-06-16 SW_22_SX1276_mbed_shield__WIN - SPI bug fixed
2018-06-16 SW_22_SX1276_mbed_shield__WIN - spreading factor bug fixed
2018-06-16 SW_22_SX1276_mbed_shield__WIN - clean-ups of the day
2018-06-17 SW_22_SX1276_mbed_shield__WIN - where is the RX packet?
2018-06-18 SW_22_SX1276_mbed_shield__WIN - first LoRa packets coming in
2018-06-19 SW_22_SX1276_mbed_shield__WIN - Bugfix 2013-09 Rev.1 Section 2.3 - Receiver Spurious Reception of a LoRa Signal added
2018-06-21 SW_22_SX1276_mbed_shield__WIN - decoding the JOIN-ACCEPT message
2018-06-21 SW_22_SX1276_mbed_shield__WIN - JOIN-ACCEPT calc session keys
2018-06-23 SW_22_SX1276_mbed_shield__WIN - refactored LoRaWAN module to run with a FSM
2018-06-25 SW_22_SX1276_mbed_shield__WIN - refactoring done, debugging follows
2018-06-25 SW_22_SX1276_mbed_shield__WIN - bug hunting neer case Fsm_RX1
2018-06-26 SW_22_SX1276_mbed_shield__WIN - RX1-->RX2 optimizations done, bugs in decoder section...
2018-06-27 SW_22_SX1276_mbed_shield__WIN - 2 bad timings within JoinRequest_RX1/RX2 fixed
2018-06-28 SW_22_SX1276_mbed_shield__WIN - power calibrations starting
2018-06-28 SW_22_SX1276_mbed_shield__WIN - simulation data for upload created
2018-06-29 SW_22_SX1276_mbed_shield__WIN - TX message structure simplified
2018-06-30 SW_22_SX1276_mbed_shield__WIN - third RX packet comes in when data TX before is replaced by Fsm_MAC_LinkCheckReq
2018-06-30 SW_22_SX1276_mbed_shield__WIN - debugging instrumentation disabled
2018-07-01 SW_22_SX1276_mbed_shield__WIN - some link information added
2018-07-01 SW_22_SX1276_mbed_shield__WIN - new MAC command NewChannelReq/NewChannelAns added
2018-07-02 SW_22_SX1276_mbed_shield__WIN - interpreter - push command for data uplink to LoRa TTN
2018-07-04 SW_22_SX1276_mbed_shield__WIN - inter-tasks IPC refactored, still not finished
2018-07-05 SW_22_SX1276_mbed_shield__WIN - UART3 for GPS added
2018-07-08 SW_22_SX1276_mbed_shield__WIN - GPS RX data working
2018-07-09 SW_22_SX1276_mbed_shield__WIN - GPS NMEA messages ready, back to LoRa transmitter
2018-07-10 SW_22_SX1276_mbed_shield__WIN - some finer tweaks for TIM5 (1PPS) done
2018-07-12 SW_22_SX1276_mbed_shield__WIN - chaining TIM4/TIM3/TIM5 still not working yet
2018-07-13 SW_22_SX1276_mbed_shield__WIN - chaining TIM4/TIM3/TIM5 hardware bug? No solution for HW-chaining
2018-07-14 SW_22_SX1276_mbed_shield__WIN - oscillator tuning works
2018-07-14 SW_22_SX1276_mbed_shield__WIN - UN*X time +1
2018-07-14 SW_22_SX1276_mbed_shield__WIN - buffer overflow fixed
2018-07-15 SW_22_SX1276_mbed_shield__WIN - STM32Cube update to 4.26 and FW to V1.12.0
2018-07-17 SW_21_SX1272_mbed_shield__WIN - SX1276 --> SX1272 changes
2018-07-17 SW_22_SX1276_mbed_shield__WIN - 1PPS red LED indication added
2018-07-29 SW_22_SX1276_mbed_shield__WIN - global enable (mode) bitmask added
2018-07-30 SW - LoRa bare mode - interpreter to LoRaWAN messages connected
2018-07-30 SW - LoRa bare mode - ready for transmission
2018-07-31 SW - LoRa bare mode - rx 1 does fail to take frequency from bare context
2018-08-01 SW_22_SX1276_mbed_shield__WIN - spiSX127xGetMode(void) insead of spiSX1276GetMode(void)
2018-08-02 SW_22_SX1276_mbed_shield__WIN - RX bare - data rate settings fixed
2018-08-03 SW_22_SX1276_mbed_shield__WIN - bad merge fixes done
2019-02-23 SW_21_SX1272 - Atollic upgrade 9.3.0 and MX update

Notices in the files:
FindMeSAT_SW/FindMeSAT_SW/src/ASF/common/boards/user_board/user_board.h:
Copyright (c) 2017 Ulrich Habel (DF4IAH). All rights reserved.
